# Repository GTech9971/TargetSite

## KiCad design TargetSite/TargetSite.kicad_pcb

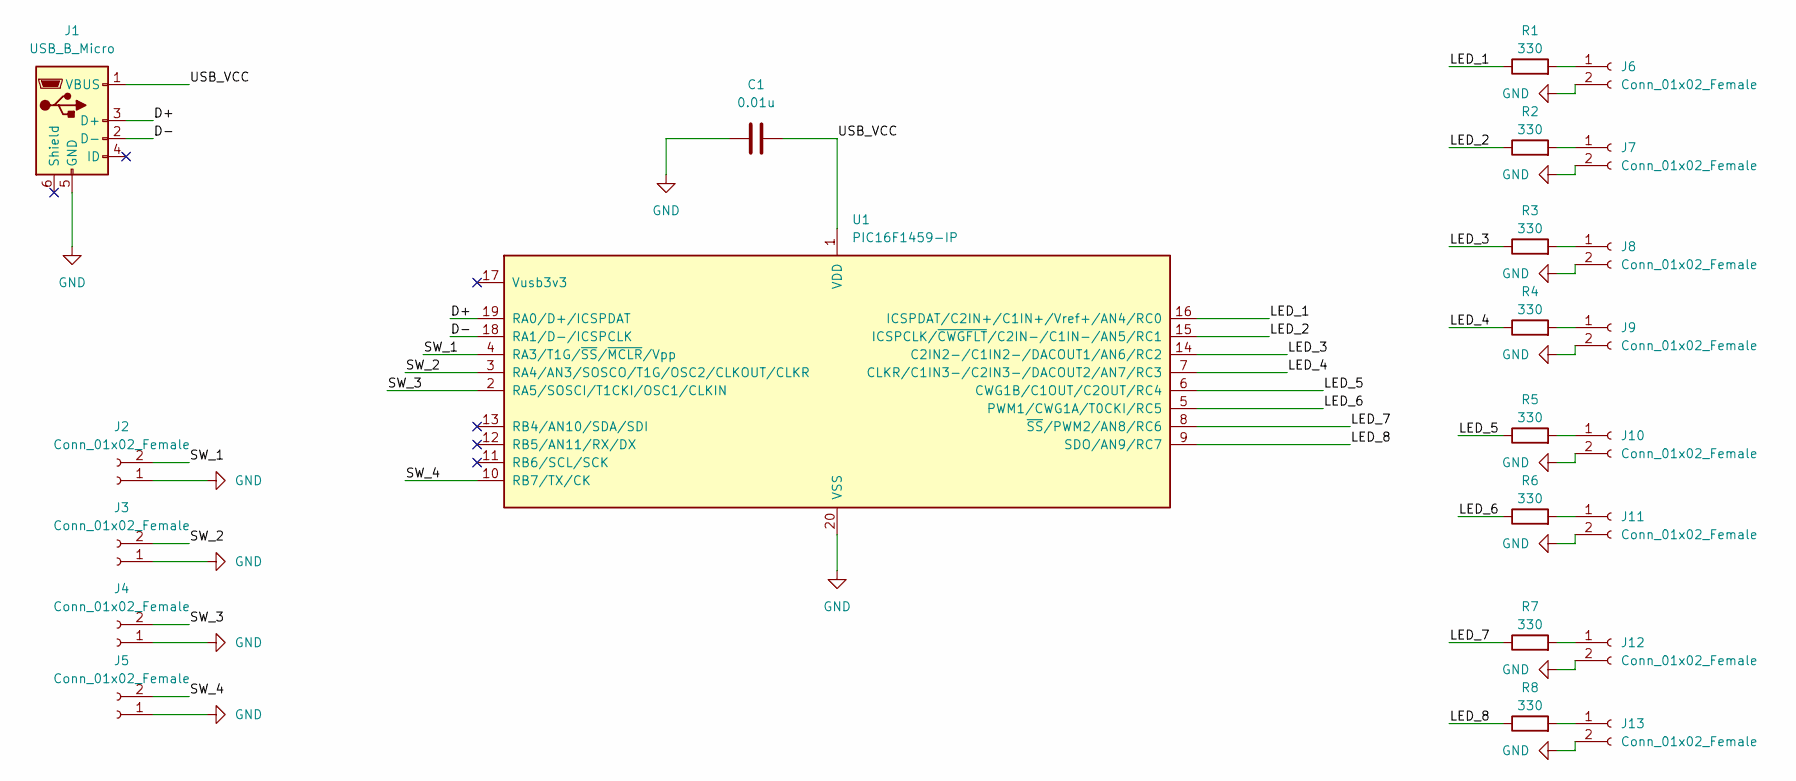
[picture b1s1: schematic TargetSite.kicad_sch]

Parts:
C1: 0.01u; C_Disc_D3.0mm_W1.6mm_P2.50mm
J1: USB_B_Micro; USB_Micro-B_Molex_47346-0001
J2, J3, J4, J5, J6, J7, J8, J9, J10, J11, J12, J13: Conn_01x02_Female; Hirose_DF13-02P-1.25DSA_1x02_P1.25mm_Vertical
R1, R2, R3, R4, R5, R6, R7, R8: 330; R_Axial_DIN0204_L3.6mm_D1.6mm_P7.62mm_Horizontal
U1: PIC16F1459-IP; DIP-20_W7.62mm

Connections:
/D+: J1.3 (D+), U1.19 (RA0/D+/ICSPDAT)
/D-: J1.2 (D-), U1.18 (RA1/D-/ICSPCLK)
/LED_1: R1.1, U1.16 (ICSPDAT/C2IN+/C1IN+/Vref+/AN4/RC0)
/LED_2: R2.1, U1.15 (ICSPCLK/~CWGFLT/C2IN-/C1IN-/AN5/RC1)
/LED_3: R3.1, U1.14 (C2IN2-/C1IN2-/DACOUT1/AN6/RC2)
/LED_4: R4.1, U1.7 (CLKR/C1IN3-/C2IN3-/DACOUT2/AN7/RC3)
/LED_5: R5.1, U1.6 (CWG1B/C1OUT/C2OUT/RC4)
/LED_6: R6.1, U1.5 (PWM1/CWG1A/T0CKI/RC5)
/LED_7: R7.1, U1.8 (~SS/PWM2/AN8/RC6)
/LED_8: R8.1, U1.9 (SDO/AN9/RC7)
/SW_1: J2.2, U1.4 (RA3/T1G/~SS/~MCLR/Vpp)
/SW_2: J3.2, U1.3 (RA4/AN3/SOSCO/T1G/OSC2/CLKOUT/CLKR)
/SW_3: J4.2, U1.2 (RA5/SOSCI/T1CKI/OSC1/CLKIN)
/SW_4: J5.2, U1.10 (RB7/TX/CK)
/USB_VCC: C1.2, J1.1 (VBUS), U1.1 (VDD)
GND: C1.1, J1.5 (GND), J2.1, J3.1, J4.1, J5.1, J6.2, J7.2, J8.2, J9.2, J10.2, J11.2, J12.2, J13.2, U1.20 (VSS)
unnamed: J6.1, R1.2
unnamed: J7.1, R2.2
unnamed: J8.1, R3.2
unnamed: J9.1, R4.2
unnamed: J10.1, R5.2
unnamed: J11.1, R6.2
unnamed: J12.1, R7.2
unnamed: J13.1, R8.2

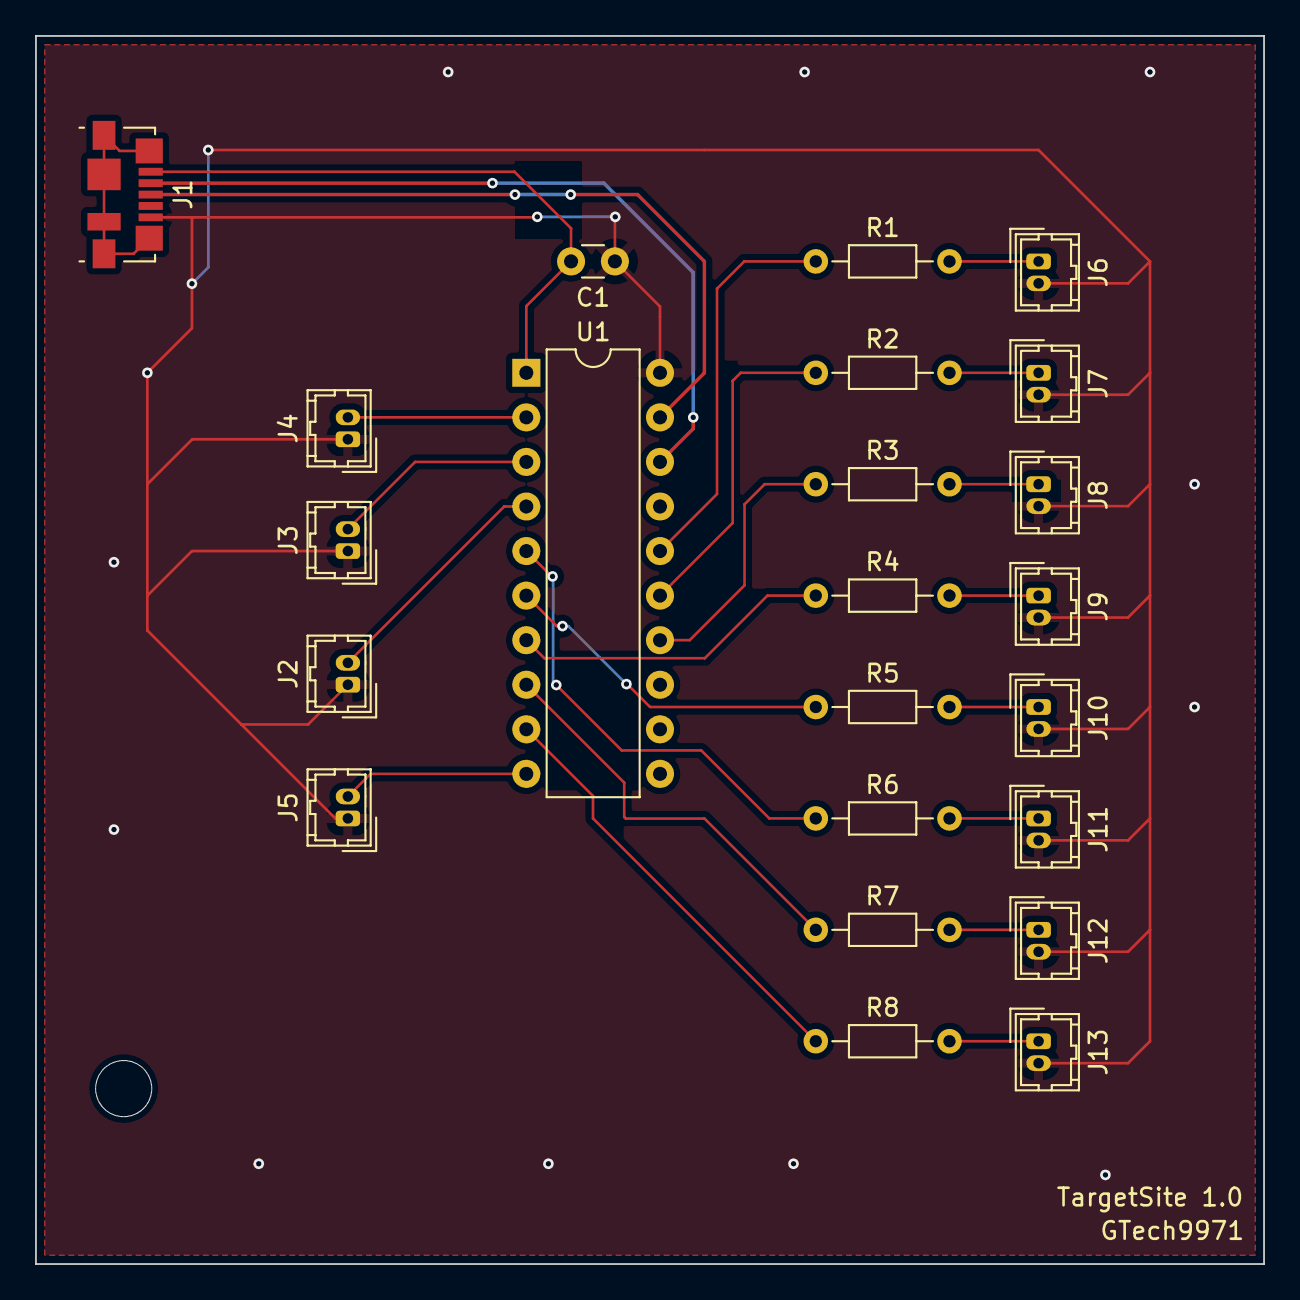
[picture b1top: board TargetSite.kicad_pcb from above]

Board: 2 copper layers, 70.0 x 70.0 mm, 24 parts (0 on the bottom side), 24 nets.

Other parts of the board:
MH1: MountingHole_3.2mm_M3

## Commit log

2022-07-01 基本ファイルを追加
2022-07-01 スタートアップ
2022-07-10 赤外線通信プログラム追加
2022-07-23 シューティング通信プログラム実装(未テスト)
    回路図追加
2022-07-24 PCB回路作成中
2022-07-28 ガーバーデータの作成、発注
